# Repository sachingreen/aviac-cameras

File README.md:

# Aviac cameras

One repository for Aviac Technologies' drone camera payloads. Each camera has its own folder under `cameras/`.
The scripts that generate the schematic, board, 3D model, renders and teardown page are written to be reused:
a new camera starts from an existing folder and changes the parts list, layout and dimensions.

| Camera | Folder | State |
| --- | --- | --- |
| 6-band crop-mapping camera (IMX565 + 3 x Mira220, Jetson Orin Nano) | `cameras/6band/` | Concept model, schematic passes ERC, board is a first routing pass. Not ready for manufacture. |
| Duo: compact stereo box for spray drones (2 x Mira220, Jetson Orin Nano, no fan) | `cameras/duo/` | Concept model, cooling and stereo calculations, spray-check method. Uses the shared carrier with two camera ports fitted. |

Shared between cameras:

| Path | What it is |
| --- | --- |
| `boards/orin-carrier/` | Jetson Orin Nano carrier: netlist (`design.py`), placement, routing, KiCad project, BOM per camera (`variants.py`) |
| `boards/mira220-module/` | Mira220 camera module extracted from the SincereFirst schematic, with the hardware trigger added |
| `toolkit/kicad/` | Schematic generator and KiCad library helpers used by every board |
| `toolkit/render/` | Blender studio renderer and denoiser used by every camera |

## What each camera folder holds

| Path | What it is |
| --- | --- |
| `docs/` | Interface findings and design notes |
| `refs/` | Supplied schematics, datasheets |
| `mechanical/` | `build_model.py` (CadQuery), outputs in `out/` |
| `renders/` | Finished studio renders |
| `teardown/` | Interactive teardown page: `src/`, `build.mjs`, built page in `dist/` |

## Rebuilding

Tools: KiCad 8, Python 3 with CadQuery, Blender 4, Node 20, Java (for the Freerouting autorouter), Intel Open Image Denoise.

```bash
python3 toolkit/kicad/gen_sch.py boards/orin-carrier
```

```bash
cd boards/orin-carrier && /usr/bin/python3 gen_pcb.py && /usr/bin/python3 route.py --export
```

```bash
python3 toolkit/kicad/gen_sch.py boards/mira220-module
```

Each camera's README has its model, render and page steps. The 3D board file (`*.glb`) is not stored; export it with `kicad-cli pcb export glb --subst-models --include-tracks`.

## Credits

- Teardown page structure and `teardown/kit/` files: [elvarofficial/teardown](https://github.com/elvarofficial/teardown), MIT.
- Jetson socket and M.2 footprints, module pin names: [antmicro/jetson-orin-baseboard](https://github.com/antmicro/jetson-orin-baseboard), Apache-2.0.

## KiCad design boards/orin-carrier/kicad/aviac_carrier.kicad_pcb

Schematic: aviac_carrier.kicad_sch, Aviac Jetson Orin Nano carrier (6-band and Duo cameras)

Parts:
C1, C2, C5, C7, C10, C15, C16, C19, C29, C61: 100n; C_0603_1608Metric; MPN CAP 100n 50V X7R 0603
C3, C4: 22u; C_1210_3225Metric; MPN CAP 22u 50V X7R 1210
C6, C23, C31, C33, C35, C37, C38, C39, C40, C41, C43, C46, C47, C48, C51, C52, C54, C60, C62: 100n; C_0402_1005Metric; MPN CAP 100n 16V X7R 0402
C8, C17: 1u; C_0603_1608Metric; MPN CAP 1u 16V X7R 0603
C9, C18: 10u; C_1210_3225Metric; MPN CAP 10u 50V X7R 1210
C11, C20: 22p; C_0402_1005Metric; MPN CAP 22p 50V C0G 0402
C12, C13, C14, C27, C28: 22u; C_1210_3225Metric; MPN CAP 22u 25V X7R 1210
C21, C22, C58, C59: 22u; C_0805_2012Metric; MPN CAP 22u 10V X5R 0805
C24: 1u; C_0603_1608Metric; MPN CAP 1u 25V X7R 0603
C25, C53: 10n; C_0402_1005Metric; MPN CAP 10n 16V X7R 0402
C26, C55: 2u2; C_0603_1608Metric; MPN CAP 2u2 10V X7R 0603
C30, C32, C34, C36, C50: 10u; C_0603_1608Metric; MPN CAP 10u 10V X5R 0603
C42: 4u7; C_0603_1608Metric; MPN CAP 4u7 10V X5R 0603
C44, C45: 12p; C_0402_1005Metric; MPN CAP 12p 50V C0G 0402
C49: 100p; C_0402_1005Metric; MPN CAP 100p 50V C0G 0402
C56, C57: 220n; C_0402_1005Metric; MPN CAP 220n 10V X5R 0402
D1: SMBJ26CA; D_SMB; MPN SMBJ26CA
D2: green; LED_0402_1005Metric; MPN LTST-C281KGKT
D3: amber; LED_0402_1005Metric; MPN LTST-C281KFKT
D4: PESD3V3L4UG; SOT-353_SC-70-5; MPN PESD3V3L4UG,115
FB1, FB2, FB3, FB4, FB5: 600R 1A; L_0603_1608Metric; MPN BLM18KG601SN1D
H1, H2: M2.5 standoff 6.5 mm; MountingHole_2.7mm_M2.5_Pad; MPN 9774065151R
H3: M2 SSD standoff 2230; MountingHole_2.2mm_M2_DIN965_Pad; MPN 9774025243R
H4, H5, H6, H7: M2.5 board mount; MountingHole_2.7mm_M2.5_Pad
J1: XT30PW-M; AMASS_XT30PW-M_1x02_P2.50mm_Horizontal; MPN XT30PW-M
J2: Jetson Orin Nano 8GB; TE_2309413; MPN 2309413-1
J3: CAM0: RGB, IMX565 (via adapter) (mirrored); Hirose_FH12-22S-0.5SH_1x22-1MP_P0.50mm_Horizontal; MPN FH12-22S-0.5SH(55)
J4: CAM1: red edge, Mira220; Hirose_FH12-22S-0.5SH_1x22-1MP_P0.50mm_Horizontal; MPN FH12-22S-0.5SH(55)
J5: CAM2: NIR, Mira220 (mirrored); Hirose_FH12-22S-0.5SH_1x22-1MP_P0.50mm_Horizontal; MPN FH12-22S-0.5SH(55)
J6: CAM3: extended NIR, Mira220; Hirose_FH12-22S-0.5SH_1x22-1MP_P0.50mm_Horizontal; MPN FH12-22S-0.5SH(55)
J7: SWD (Tag-Connect); Tag-Connect_TC2030-IDC-NL_2x03_P1.27mm_Vertical; MPN (no part: PCB pads for TC2030-IDC-NL ca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
J8: TELEM (MAVLink); JST_GH_SM06B-GHS-TB_1x06-1MP_P1.25mm_Horizontal; MPN SM06B-GHS-TB
J9: CAM TRIGGER; JST_GH_SM04B-GHS-TB_1x04-1MP_P1.25mm_Horizontal; MPN SM04B-GHS-TB
J10: GNSS ANT; U.FL_Hirose_U.FL-R-SMT-1_Vertical; MPN U.FL-R-SMT-1(10)
J11: M.2 Key M; Bus_M.2_Socket_Key_M_TE_1-2199230-6; MPN 1-2199230-6
J12: USB-C; USB_C_Receptacle_GCT_USB4105-xx-A_16P_TopMnt_Horizontal; MPN USB4105-GF-A
J13: DLS; JST_GH_SM05B-GHS-TB_1x05-1MP_P1.25mm_Horizontal; MPN SM05B-GHS-TB
J14: DEBUG UART 1V8 DNP; PinHeader_1x03_P1.27mm_Vertical; MPN (not fitted); not fitted
L1: 6u8 8A; L_Bourns_SRP6060FA; MPN SRP6060FA-6R8M
L2: 6u8 3.9A; L_Coilcraft_XAL4030-XXX; MPN XAL4030-682ME
L3: 27n; L_0402_1005Metric; MPN LQG15HS27NJ02D
Q1: BSC028N06LS3; TDSON-8-1; MPN BSC028N06LS3GATMA1
Q2: 2N7002; SOT-23; MPN 2N7002NXAKR
R1, R3, R5, R7, R8, R10, R12, R14, R16, R18, R22, R26, R30, R42, R44, R51, R55: 100k; R_0402_1005Metric; MPN RES 100k 1% 0402
R2: 6k8; R_0402_1005Metric; MPN RES 6k8 1% 0402
R4: 16k2; R_0402_1005Metric; MPN RES 16k2 1% 0402
R6: 15k4; R_0402_1005Metric; MPN RES 15k4 1% 0402
R9: 43k2; R_0402_1005Metric; MPN RES 43k2 1% 0402
R11, R17, R34, R40, R45: 10k; R_0402_1005Metric; MPN RES 10k 1% 0402
R13, R37, R38, R39, R41: 1k; R_0402_1005Metric; MPN RES 1k 1% 0402
R15, R47, R48: 47k; R_0402_1005Metric; MPN RES 47k 1% 0402
R19, R20, R23, R24, R27, R28, R31, R32, R53, R54: 2k2; R_0402_1005Metric; MPN RES 2k2 1% 0402
R21, R25, R29, R33: 33R; R_0402_1005Metric; MPN RES 33R 1% 0402
R35, R36: 2k2 DNP; R_0402_1005Metric; MPN RES 2k2 1% 0402; not fitted
R43: 100R; R_0402_1005Metric; MPN RES 100R 1% 0402
R46: 10R; R_0402_1005Metric; MPN RES 10R 1% 0402
R49, R50: 5k1; R_0402_1005Metric; MPN RES 5k1 1% 0402
R52: 56k; R_0402_1005Metric; MPN RES 56k 1% 0402
SW1: RECOVERY; SW_SPST_B3U-1000P-B; MPN B3U-1000P-B
SW2: RESET; SW_SPST_B3U-1000P-B; MPN B3U-1000P-B
TP1: VSYS; TestPoint_Pad_D1.0mm
TP2: 3V3; TestPoint_Pad_D1.0mm
TP3: 1V8; TestPoint_Pad_D1.0mm
TP4: GND; TestPoint_Pad_D1.0mm
U1: LM74700-Q1; SOT-23-6; MPN LM74700QDBVRQ1
U2: LMR33640ADDA; Texas_HSOP-8-1EP_3.9x4.9mm_P1.27mm_ThermalVias; MPN LMR33640ADDAR
U3: LMR33630ADDA; Texas_HSOP-8-1EP_3.9x4.9mm_P1.27mm_ThermalVias; MPN LMR33630ADDAR
U4: LP2985-18; SOT-23-5; MPN LP2985-18DBVR
U5: TCA9548A; TSSOP-24_4.4x7.8mm_P0.65mm; MPN TCA9548APWR
U6: STM32G0B1CBT6; LQFP-48_7x7mm_P0.5mm; MPN STM32G0B1CBT6
U7: TXS0102; VSSOP-8_2.3x2mm_P0.5mm; MPN TXS0102DCUR
U8: 74LVC2G17; SOT-363_SC-70-6; MPN SN74LVC2G17DCKR
U9: MAX-M10S; ublox_MAX; MPN MAX-M10S-00B
U10: ICM-42688-P; LGA-14_3x2.5mm_P0.5mm_LayoutBorder3x4y; MPN ICM-42688-P
U11: USBLC6-2SC6; SOT-23-6; MPN USBLC6-2SC6
U12: M24C02-F; SOIC-8_3.9x4.9mm_P1.27mm; MPN M24C02-FMN6TP
Y1: 8MHz; Crystal_SMD_3225-4Pin_3.2x2.5mm; MPN ABM8-8.000MHZ-10-D1G-T

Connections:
+1V8: C26.1, C38.1, C39.1, C40.1, C41.1, C42.1, C46.1, C48.1, C52.1, C54.1, C55.1, C62.1, J7.1, J13.1, R16.1, R19.1, R20.1, R23.1, R24.1, R27.1, R28.1, R31.1, R32.1, R34.1, R35.1, R36.1, R40.1, R53.1, R54.1, R55.1, TP3.1, U4.5 (VOUT), U5.24 (VCC), U6.4 (VBAT), U6.5 (VREF+), U6.6 (VDD), U7.3 (VCCA), U8.5 (VCC), U9.6 (V_BCKP), U9.7 (VCC_IO), U10.5 (VDDIO), U10.8 (VDD), U12.1 (E0), U12.2 (E1), U12.3 (E2), U12.8 (VCC)
+3V3: C20.1, C21.1, C22.1, C23.1, C47.1, C58.1, C59.1, C60.1, D2.2 (A), FB1.1, FB2.1, FB3.1, FB4.1, FB5.1, J11.2 (3.3V), J11.4 (3.3V), J11.12 (3.3V), J11.14 (3.3V), J11.16 (3.3V), J11.18 (3.3V), J11.70 (3.3V), J11.72 (3.3V), J11.74 (3.3V), L2.2, R8.1, R39.1, R45.1, R47.1, R48.1, TP2.1, U7.7 (VCCB)
CAM0_3V3: C30.1, C31.1, FB1.2, J3.1
CAM0_CLK_N: J2.10 (CSI0_CLK_N), J3.15
CAM0_CLK_P: J2.12 (CSI0_CLK_P), J3.14
CAM0_D0_N: J2.4 (CSI0_D0_N), J3.21
CAM0_D0_P: J2.6 (CSI0_D0_P), J3.20
CAM0_D1_N: J2.16 (CSI0_D1_N), J3.18
CAM0_D1_P: J2.18 (CSI0_D1_P), J3.17
CAM0_EN: J2.114 (CAM0_PWDN), J3.6, R18.1
CAM0_SCL: J3.3, R19.2, U5.5 (SC0)
CAM0_SDA: J3.2, R20.2, U5.4 (SD0)
CAM0_TRIG: J3.5, R21.2
CAM1_3V3: C32.1, C33.1, FB2.2, J4.22
CAM1_CLK_N: J2.9 (CSI1_CLK_N), J4.8
CAM1_CLK_P: J2.11 (CSI1_CLK_P), J4.9
CAM1_D0_N: J2.3 (CSI1_D0_N), J4.2
CAM1_D0_P: J2.5 (CSI1_D0_P), J4.3
CAM1_D1_N: J2.15 (CSI1_D1_N), J4.5
CAM1_D1_P: J2.17 (CSI1_D1_P), J4.6
CAM1_EN: J2.120 (CAM1_PWDN), J4.17, R22.1
CAM1_SCL: J4.20, R23.2, U5.7 (SC1)
CAM1_SDA: J4.21, R24.2, U5.6 (SD1)
CAM1_TRIG: J4.18, R25.2
CAM2_3V3: C34.1, C35.1, FB3.2, J5.1
CAM2_CLK_N: J2.28 (CSI2_CLK_N), J5.15
CAM2_CLK_P: J2.30 (CSI2_CLK_P), J5.14
CAM2_D0_N: J2.22 (CSI2_D0_N), J5.21
CAM2_D0_P: J2.24 (CSI2_D0_P), J5.20
CAM2_D1_N: J2.34 (CSI2_D1_N), J5.18
CAM2_D1_P: J2.36 (CSI2_D1_P), J5.17
CAM2_EN: J2.124 (GPIO02), J5.6, R26.1
CAM2_SCL: J5.3, R27.2, U5.9 (SC2)
CAM2_SDA: J5.2, R28.2, U5.8 (SD2)
CAM2_TRIG: J5.5, R29.2
CAM3_3V3: C36.1, C37.1, FB4.2, J6.22
CAM3_CLK_N: J2.27 (CSI3_CLK_N), J6.8
CAM3_CLK_P: J2.29 (CSI3_CLK_P), J6.9
CAM3_D0_N: J2.21 (CSI3_D0_N), J6.2
CAM3_D0_P: J2.23 (CSI3_D0_P), J6.3
CAM3_D1_N: J2.33 (CSI3_D1_N), J6.5
CAM3_D1_P: J2.35 (CSI3_D1_P), J6.6
CAM3_EN: J2.126 (GPIO03), J6.17, R30.1
CAM3_SCL: J6.20, R31.2, U5.11 (SC3)
CAM3_SDA: J6.21, R32.2, U5.10 (SD3)
CAM3_TRIG: J6.18, R33.2
DBG_RX: J2.238 (UART2_RXD), J14.2
DBG_TX: J2.236 (UART2_TXD), J14.1
DLS_INT: J13.4, R55.2, U6.21 (PB2)
DLS_SCL: J13.2, R53.2, U6.47 (PB8)
DLS_SDA: J13.3, R54.2, U6.48 (PB9)
FC_FB_GATE: Q2.1 (G), R44.1, U6.20 (PB1)
FC_FB_OUT: D4.5 (K4), J9.2, Q2.3 (D), R45.2
FC_TRIG_1V8: U6.12 (PA1), U8.6
FC_TRIG_IN: D4.4 (K3), J9.1, R41.1
FC_TRIG_IN_F: C49.1, R41.2, R42.1, U8.1
FORCE_RECOVERY_N: J2.214 (FORCE_RECOVERY*), SW1.1
FRAME_SYNC: J2.216 (GPIO11/CLK), U6.44 (PB5)
GND: C2.2, C3.2, C4.2, C5.2, C6.2, C8.2, C9.2, C10.2, C12.2, C13.2, C14.2, C15.2, C17.2, C18.2, C19.2, C21.2, C22.2, C23.2, C24.2, C25.2, C26.2, C27.2, C28.2, C29.2, C30.2, C31.2, C32.2, C33.2, C34.2, C35.2, C36.2, C37.2, C38.2, C39.2, C40.2, C41.2, C42.2, C43.2, C44.2, C45.2, C46.2, C47.2, C48.2, C49.2, C50.2, C51.2, C52.2, C53.2, C54.2, C55.2, C58.2, C59.2, C60.2, C61.2, C62.2, D1.2 (A2), D4.2 (A), H1.1, H2.1, H3.1, H4.1, H5.1, H6.1, H7.1, J1.2, J2.1 (GND), J2.2 (GND), J2.7 (GND), J2.8 (GND), J2.13 (GND), J2.14 (GND), J2.19 (GND), J2.20 (GND), J2.25 (GND), J2.26 (GND), J2.31 (GND), J2.32 (GND), J2.37 (GND), J2.38 (GND), J2.43 (GND), J2.44 (GND), J2.49 (GND), J2.50 (GND), J2.55 (GND), J2.56 (GND), J2.61 (GND), J2.62 (GND), J2.67 (GND), J2.68 (GND), J2.73 (GND), J2.74 (GND), J2.79 (GND), J2.80 (GND), J2.85 (GND), J2.86 (GND), J2.102 (GND), J2.107 (GND), J2.113 (GND), J2.119 (GND), J2.125 (GND), J2.129 (GND), J2.132 (GND), J2.135 (GND), J2.138 (GND), J2.141 (GND), J2.144 (GND), J2.146 (GND), J2.147 (GND), J2.152 (GND), J2.153 (GND), J2.158 (GND), J2.159 (GND), J2.164 (GND), J2.165 (GND), J2.170 (GND), J2.171 (GND), J2.176 (GND), J2.177 (GND), J2.200 (GND), J2.201 (GND), J2.231 (GND), J2.241 (GND), J2.242 (GND), J2.243 (GND), J2.244 (GND), J2.245 (GND), J2.246 (GND), J2.247 (GND), J2.248 (GND), J2.249 (GND), J2.250 (GND), J3.4, J3.7, J3.10, J3.13, J3.16, J3.19, J3.22, J3.MP (MountPin), J4.1, J4.4, J4.7, J4.10, J4.13, J4.16, J4.19, J4.MP (MountPin), J5.4, J5.7, J5.10, J5.13, J5.16, J5.19, J5.22, J5.MP (MountPin), J6.1, J6.4, J6.7, J6.10, J6.13, J6.16, J6.19, J6.MP (MountPin), J7.5, J8.6, J8.MP (MountPin), J9.4, J9.MP (MountPin), J10.2 (Ext), J11.1 (GND), J11.3 (GND), J11.9 (GND), J11.15 (GND), J11.21 (GND), J11.27 (GND), J11.33 (GND), J11.39 (GND), J11.45 (GND), J11.51 (GND), J11.57 (GND), J11.71 (GND), J11.73 (GND), J11.75 (GND), J11.MP1, J11.MP2, J12.A1 (GND), J12.A12 (GND), J12.B1 (GND), J12.B12 (GND), J12.S1 (SHIELD), J13.5, J13.MP (MountPin), J14.3, Q2.2 (S), R2.2, R4.2, R6.2, R9.2, R12.2, R13.2, R15.2, R18.2, R22.2, R26.2, R30.2, R42.2, R44.2, R49.2, R50.2, R52.2, SW1.2, SW2.2, TP4.1, U1.2 (GND), U2.1 (GND), U2.9 (GND), U3.1 (GND), U3.9 (GND), U4.2 (GND), U5.1 (A0), U5.2 (A1), U5.12 (GND), U5.21 (A2), U6.7 (VSS), U7.2 (GND), U8.2 (GND), U9.1 (GND), U9.10 (GND), U9.12 (GND), U9.15 (VIO_SEL), U10.6 (GND), U11.2 (GND), U12.4 (VSS), U12.7 (~WC), Y1.2, Y1.4
GNSS_BIAS: C53.1, L3.1, R46.2
GNSS_RF: J10.1 (In), L3.2, U9.11 (RF_IN)
GNSS_RXD: U6.22 (PB10), U9.3 (RXD)
GNSS_TXD: U6.23 (PB11), U9.2 (TXD)
GNSS_VCC: C50.1, C51.1, FB5.2, U9.8 (VCC)
GNSS_VCC_RF: R46.1, U9.14 (VCC_RF)
I2C_CAM_SCL: J2.213 (CAM_I2C_SCL), R35.2, U5.22 (SCL)
I2C_CAM_SDA: J2.215 (CAM_I2C_SDA), R36.2, U5.23 (SDA)
I2C_ID_SCL: J2.232 (I2C2_SCL), U12.6 (SCL)
I2C_ID_SDA: J2.234 (I2C2_SDA), U12.5 (SDA)
I2C_MUX_RST_N: R34.2, U5.3 (~RESET)
IMU_CS_N: U6.15 (PA4), U10.12 (AP_CS)
IMU_INT1: U6.19 (PB0), U10.4 (INT1)
IMU_MISO: U6.17 (PA6), U10.1 (AP_SDO)
IMU_MOSI: U6.18 (PA7), U10.14 (AP_SDI)
IMU_SCK: U6.16 (PA5), U10.13 (AP_SCLK)
LDO_BP: C25.1, U4.4 (BP)
LED_PWR_K: D2.1 (K), R13.1
LED_STAT_A: D3.2 (A), R39.2
LED_STAT_K: D3.1 (K), U6.24 (PB12)
MCU_BOOT_REQ: J2.228 (GPIO13/PWM), R38.1
MCU_NRST: C43.1, J7.3, R37.2, U6.10 (PF2)
MCU_NRST_REQ: J2.218 (GPIO12/PWM), R37.1
MCU_OSC_IN: C44.1, U6.8 (PF0), Y1.1
MCU_OSC_OUT: C45.1, U6.9 (PF1), Y1.3
MCU_UART_RX: J2.99 (UART0_TXD), U6.14 (PA3)
MCU_UART_TX: J2.101 (UART0_RXD), U6.13 (PA2)
P3V3_BOOT: C16.1, U3.7 (BOOT)
P3V3_EN: R11.2, R12.1, U3.3 (EN)
P3V3_FB: C20.2, R8.2, R9.1, U3.5 (FB)
P3V3_PG: R10.2, U3.4 (PG)
P3V3_SW: C16.2, L2.1, U3.8 (SW)
P3V3_VCC: C17.1, R10.1, U3.6 (VCC)
PCIE_CLKREQ_N: J2.180 (PCIE0_CLKREQ*), J11.52 (~CLKREQ), R47.2
PCIE_CLK_N: J2.160 (PCIE0_CLK_N), J11.53 (REFCLKn)
PCIE_CLK_P: J2.162 (PCIE0_CLK_P), J11.55 (REFCLKp)
PCIE_RST_N: J2.181 (PCIE0_RST*), J11.50 (~PERST)
PCIE_RX_N: J2.131 (PCIE0_RX0_N), J11.41 (PERn0/SATA-B+)
PCIE_RX_P: J2.133 (PCIE0_RX0_P), J11.43 (PERp0/SATA-B-)
PCIE_TX_C_N: C56.1, J2.134 (PCIE0_TX0_N)
PCIE_TX_C_P: C57.1, J2.136 (PCIE0_TX0_P)
PCIE_TX_N: C56.2, J11.47 (PETn0/SATA-A-)
PCIE_TX_P: C57.2, J11.49 (PETp0/SATA-A+)
PCIE_WAKE_N: J2.179 (PCIE_WAKE*), J11.54 (~PEWAKE), R48.2
POWER_EN: J2.237 (POWER_EN), R14.2, R15.1, U6.25 (PB13)
PPS_1V8: J2.211 (GPIO09/AUD_MCLK), U6.37 (PA15), U8.3, U9.4 (TIMEPULSE)
PPS_BUF: R43.1, U8.4
PPS_OUT: J9.3, R43.2
RP_GATE: Q1.4 (G), U1.5 (GATE)
RP_VCAP: C1.1, U1.1 (VCAP)
SHUTDOWN_REQ_N: J2.233 (SHUTDOWN_REQ*), R16.2, U6.26 (PB14)
SWCLK_BOOT0: J7.4, R38.2, U6.36 (PA14)
SWDIO: J7.2, U6.35 (PA13)
SYS_RESET_N: J2.239 (SYS_RESET*), R11.1, R17.1, SW2.1
SYS_RESET_SENSE: R17.2, U6.27 (PB15)
TELEM_OE: R40.2, U7.6 (OE)
TELEM_RX_1V8: J2.205 (UART1_RXD), U7.4 (A2)
TELEM_RX_3V3: D4.1 (K1), J8.2, U7.1 (B2)
TELEM_TX_1V8: J2.203 (UART1_TXD), U7.5 (A1)
TELEM_TX_3V3: D4.3 (K2), J8.3, U7.8 (B1)
TRIG0: R21.1, U6.28 (PA8)
TRIG1: R25.1, U6.29 (PA9/UCPD1_DBCC1)
TRIG2: R29.1, U6.32 (PA10/UCPD1_DBCC2)
TRIG3: R33.1, U6.33 (PA9/PA11)
USB_CC1: J12.A5 (CC1), R49.1
USB_CC2: J12.B5 (CC2), R50.1
USB_CON_D_N: J12.A7 (D-), J12.B7 (D-), U11.1 (I/O1)
USB_CON_D_P: J12.A6 (D+), J12.B6 (D+), U11.3 (I/O2)
USB_D_N: J2.109 (USB0_D_N), U11.6 (I/O1)
USB_D_P: J2.111 (USB0_D_P), U11.4 (I/O2)
USB_VBUS: C61.1, J12.A4 (VBUS), J12.A9 (VBUS), J12.B4 (VBUS), J12.B9 (VBUS), R51.1, U11.5 (VBUS)
USB_VBUS_DET: J2.118 (GPIO01/CLK), R51.2, R52.1
VBAT: C3.1, C4.1, C5.1, C9.1, C10.1, C18.1, C19.1, Q1.5 (D), R1.1, R3.1, U1.4 (CATHODE), U2.2 (VIN), U3.2 (VIN)
VBAT_IN: C1.2, C2.1, D1.1 (A1), J1.1, Q1.1 (S), Q1.2 (S), Q1.3 (S), U1.3 (EN), U1.6 (ANODE)
VBAT_SENSE: C6.1, R1.2, R2.1, U6.11 (PA0)
VSYS: C11.1, C12.1, C13.1, C14.1, C15.1, C24.1, C27.1, C28.1, C29.1, J2.251 (VDD_IN), J2.252 (VDD_IN), J2.253 (VDD_IN), J2.254 (VDD_IN), J2.255 (VDD_IN), J2.256 (VDD_IN), J2.257 (VDD_IN), J2.258 (VDD_IN), J2.259 (VDD_IN), J2.260 (VDD_IN), L1.2, R5.1, R14.1, TP1.1, U4.1 (VIN), U4.3 (ON/~OFF)
VSYS_BOOT: C7.1, U2.7 (BOOT)
VSYS_EN: R3.2, R4.1, U2.3 (EN)
VSYS_FB: C11.2, R5.2, R6.1, U2.5 (FB)
VSYS_PG: R7.2, U2.4 (PG)
VSYS_SW: C7.2, L1.1, U2.8 (SW)
VSYS_VCC: C8.1, R7.1, U2.6 (VCC)

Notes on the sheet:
POWER INPUT 3S-6S: REVERSE-POLARITY AND SURGE PROTECTION
7.5 V 4 A MODULE SUPPLY (VSYS)
3.3 V 3 A PERIPHERAL SUPPLY AND 1.8 V ALWAYS-ON
JETSON ORIN NANO MODULE
MODULE POWER SEQUENCING, RESET AND RECOVERY
CAMERA PORTS: 4 x 2-LANE MIPI CSI-2, 22-PIN FPC
CAMERA I2C SWITCH
SYNC MICROCONTROLLER
TRIGGER FAN-OUT AND AUTOPILOT INTERFACE
GNSS RECEIVER WITH PPS
INERTIAL SENSOR
M.2 2230 NVME STORAGE
USB-C: FLASHING AND DATA
DLS PORT, DEBUG, ID EEPROM, MECHANICAL

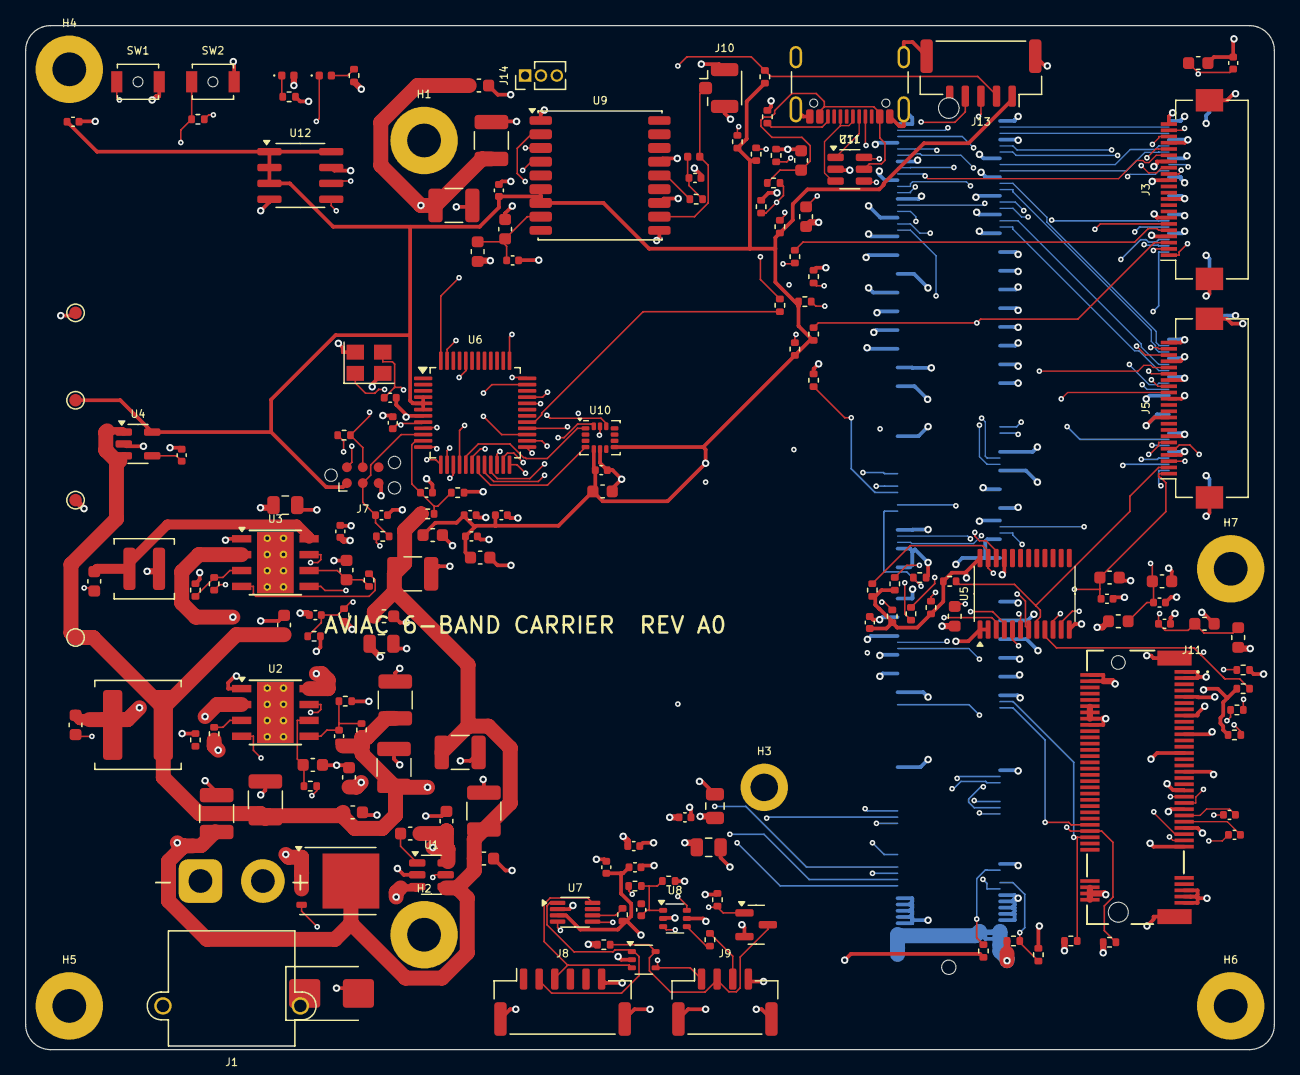
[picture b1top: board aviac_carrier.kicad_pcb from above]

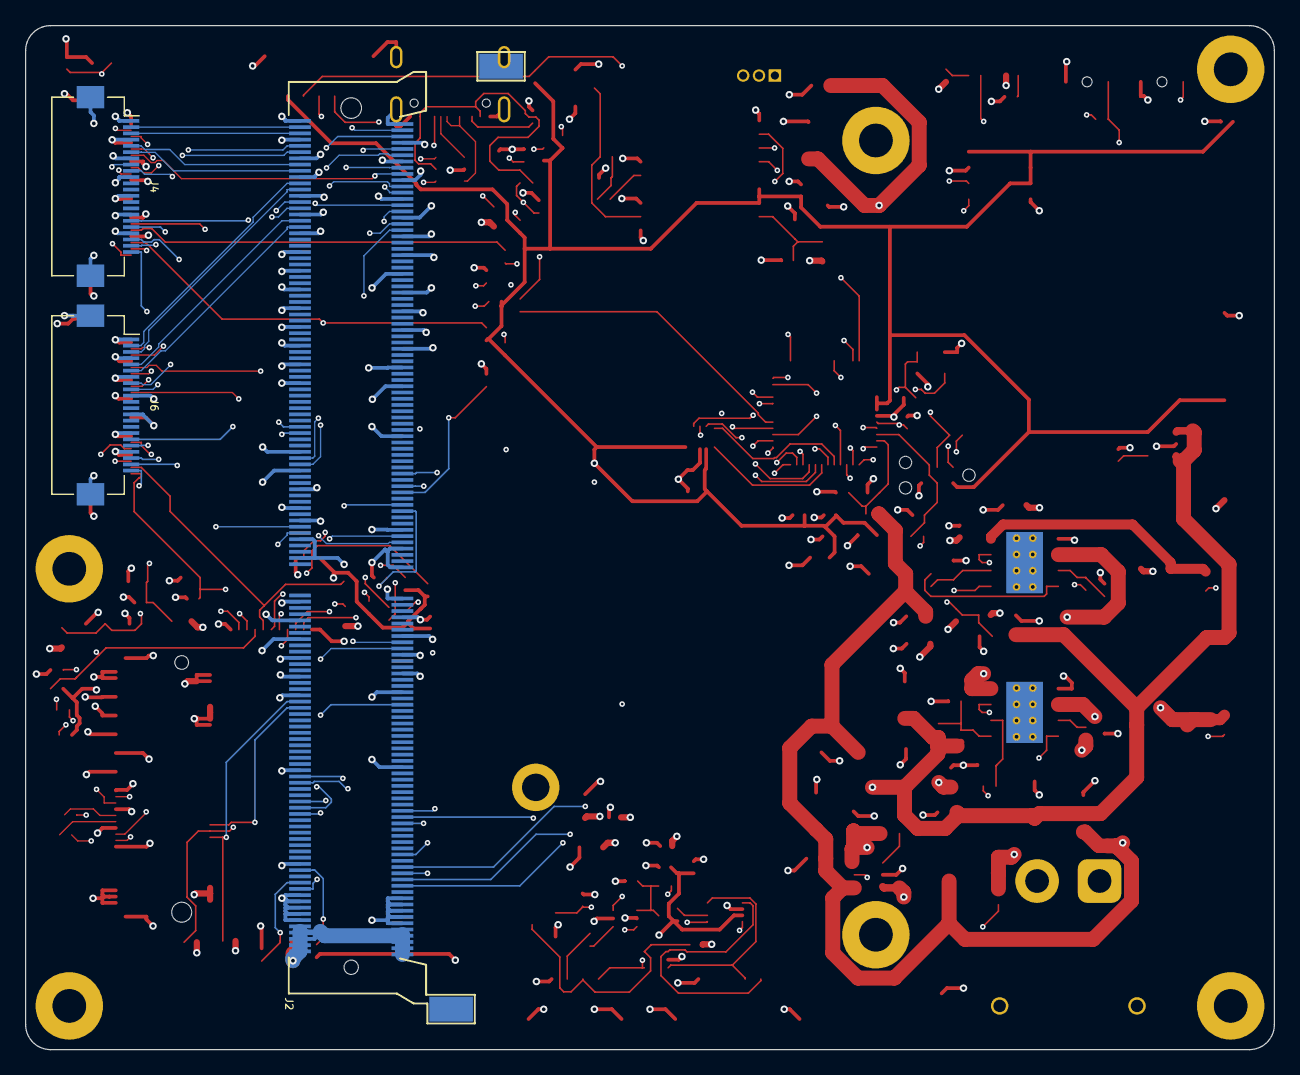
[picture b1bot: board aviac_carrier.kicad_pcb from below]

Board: 6 copper layers, 100.0 x 82.0 mm, 171 parts (3 on the bottom side), 141 nets.

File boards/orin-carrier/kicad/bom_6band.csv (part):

References,Qty,Value,Manufacturer part,Manufacturer,Description,Footprint
C1 C2 C5 C7 C10 C15 C16 C19 C29 C61,10,100n,CAP 100n 50V X7R 0603,generic (Murata GRM / Samsung CL),Capacitor 100n 50V X7R 0603,C_0603_1608Metric
C3 C4,2,22u,CAP 22u 50V X7R 1210,generic (Murata GRM / Samsung CL),Capacitor 22u 50V X7R 1210,C_1210_3225Metric
C6 C23 C31 C33 C35 C37 C38 C39 C40 C41 C43 C46 C47 C48 C51 C52 C54 C60 C62,19,100n,CAP 100n 16V X7R 0402,generic (Murata GRM / Samsung CL),Capacitor 100n 16V X7R 0402,C_0402_1005Metric
C8 C17,2,1u,CAP 1u 16V X7R 0603,generic (Murata GRM / Samsung CL),Capacitor 1u 16V X7R 0603,C_0603_1608Metric
C9 C18,2,10u,CAP 10u 50V X7R 1210,generic (Murata GRM / Samsung CL),Capacitor 10u 50V X7R 1210,C_1210_3225Metric
C11 C20,2,22p,CAP 22p 50V C0G 0402,generic (Murata GRM / Samsung CL),Capacitor 22p 50V C0G 0402,C_0402_1005Metric
C12 C13 C14 C27 C28,5,22u,CAP 22u 25V X7R 1210,generic (Murata GRM / Samsung CL),Capacitor 22u 25V X7R 1210,C_1210_3225Metric
C21 C22 C58 C59,4,22u,CAP 22u 10V X5R 0805,generic (Murata GRM / Samsung CL),Capacitor 22u 10V X5R 0805,C_0805_2012Metric
C24,1,1u,CAP 1u 25V X7R 0603,generic (Murata GRM / Samsung CL),Capacitor 1u 25V X7R 0603,C_0603_1608Metric
C25 C53,2,10n,CAP 10n 16V X7R 0402,generic (Murata GRM / Samsung CL),Capacitor 10n 16V X7R 0402,C_0402_1005Metric
C26 C55,2,2u2,CAP 2u2 10V X7R 0603,generic (Murata GRM / Samsung CL),Capacitor 2u2 10V X7R 0603,C_0603_1608Metric
C30 C32 C34 C36 C50,5,10u,CAP 10u 10V X5R 0603,generic (Murata GRM / Samsung CL),Capacitor 10u 10V X5R 0603,C_0603_1608Metric
C42,1,4u7,CAP 4u7 10V X5R 0603,generic (Murata GRM / Samsung CL),Capacitor 4u7 10V X5R 0603,C_0603_1608Metric
C44 C45,2,12p,CAP 12p 50V C0G 0402,generic (Murata GRM / Samsung CL),Capacitor 12p 50V C0G 0402,C_0402_1005Metric
C49,1,100p,CAP 100p 50V C0G 0402,generic (Murata GRM / Samsung CL),Capacitor 100p 50V C0G 0402,C_0402_1005Metric
C56 C57,2,220n,CAP 220n 10V X5R 0402,generic (Murata GRM / Samsung CL),Capacitor 220n 10V X5R 0402,C_0402_1005Metric
D1,1,SMBJ26CA,SMBJ26CA,Littelfuse,"TVS 26 V stand-off, bidirectional, 600 W",D_SMB
D2,1,green,LTST-C281KGKT,Lite-On,"LED green 0402, peripherals powered",LED_0402_1005Metric
D3,1,amber,LTST-C281KFKT,Lite-On,"LED amber 0402, sync status",LED_0402_1005Metric
D4,1,PESD3V3L4UG,"PESD3V3L4UG,115",Nexperia,4-line ESD protection for the autopilot connectors,SOT-353_SC-70-5
FB1 FB2 FB3 FB4 FB5,5,600R 1A,BLM18KG601SN1D,Murata,"Ferrite bead 600 ohm at 100 MHz, 1.3 A, 0603",L_0603_1608Metric
J1,1,XT30PW-M,XT30PW-M,AMASS,"Battery input 3S-6S (9-25.2 V), 15 A connector",AMASS_XT30PW-M_1x02_P2.50mm_Horizontal
J2,1,Jetson Orin Nano 8GB,2309413-1,TE Connectivity,"260-pin SO-DIMM socket, 9.2 mm, for Jetson Orin Nano module",TE_2309413
J3,1,"CAM0: RGB, IMX565 (via adapter) (mirrored)",FH12-22S-0.5SH(55),Hirose,"FPC connector 22-pin 0.5 mm, bottom contact",Hirose_FH12-22S-0.5SH_1x22-1MP_P0.50mm_Horizontal
J4,1,"CAM1: red edge, Mira220",FH12-22S-0.5SH(55),Hirose,"FPC connector 22-pin 0.5 mm, bottom contact",Hirose_FH12-22S-0.5SH_1x22-1MP_P0.50mm_Horizontal
J5,1,"CAM2: NIR, Mira220 (mirrored)",FH12-22S-0.5SH(55),Hirose,"FPC connector 22-pin 0.5 mm, bottom contact",Hirose_FH12-22S-0.5SH_1x22-1MP_P0.50mm_Horizontal
J6,1,"CAM3: extended NIR, Mira220",FH12-22S-0.5SH(55),Hirose,"FPC connector 22-pin 0.5 mm, bottom contact",Hirose_FH12-22S-0.5SH_1x22-1MP_P0.50mm_Horizontal
J8,1,TELEM (MAVLink),SM06B-GHS-TB,JST,"Autopilot TELEM port, Pixhawk pinout (pin 1 = 5 V not used)",JST_GH_SM06B-GHS-TB_1x06-1MP_P1.25mm_Horizontal
J9,1,CAM TRIGGER,SM04B-GHS-TB,JST,"Camera trigger in, exposure feedback out, PPS out",JST_GH_SM04B-GHS-TB_1x04-1MP_P1.25mm_Horizontal
J10,1,GNSS ANT,U.FL-R-SMT-1(10),Hirose,"U.FL antenna connector, active antenna on the top unit",U.FL_Hirose_U.FL-R-SMT-1_Vertical
J11,1,M.2 Key M,1-2199230-6,TE Connectivity,"M.2 Key-M socket, PCIe x1 (lane 0) to NVMe 2230",Bus_M.2_Socket_Key_M_TE_1-2199230-6
J12,1,USB-C,USB4105-GF-A,GCT,"USB-C receptacle, USB 2.0, device mode for flashing and data",USB_C_Receptacle_GCT_USB4105-xx-A_16P_TopMnt_Horizontal
J13,1,DLS,SM05B-GHS-TB,JST,"Downwelling light sensor port (I2C at 1.8 V, read by the sync MCU)",JST_GH_SM05B-GHS-TB_1x05-1MP_P1.25mm_Horizontal
L1,1,6u8 8A,SRP6060FA-6R8M,Bourns,"Power inductor 6.8 uH, Isat 8 A, 6.6 x 6.4 x 5.8 mm",L_Bourns_SRP6060FA
L2,1,6u8 3.9A,XAL4030-682ME,Coilcraft,"Power inductor 6.8 uH, Isat 3.9 A, 4 x 4 x 3.1 mm",L_Coilcraft_XAL4030-XXX
L3,1,27n,LQG15HS27NJ02D,Murata,"RF inductor 27 nH, antenna bias feed",L_0402_1005Metric
Q1,1,BSC028N06LS3,BSC028N06LS3GATMA1,Infineon,"N-MOSFET 60 V 2.8 mOhm, ideal-diode pass element",TDSON-8-1
Q2,1,2N7002,2N7002NXAKR,Nexperia,"N-MOSFET, open-drain exposure feedback to autopilot",SOT-23
R1 R3 R5 R7 R8 R10 R12 R14 R16 R18 R22 R26 R30 R42 R44 R51 R55,17,100k,RES 100k 1% 0402,generic (Yageo RC / Vishay CRCW),Resistor 100k 1% 0402,R_0402_1005Metric
R2,1,6k8,RES 6k8 1% 0402,generic (Yageo RC / Vishay CRCW),Resistor 6k8 1% 0402,R_0402_1005Metric
R4,1,16k2,RES 16k2 1% 0402,generic (Yageo RC / Vishay CRCW),Resistor 16k2 1% 0402,R_0402_1005Metric
R6,1,15k4,RES 15k4 1% 0402,generic (Yageo RC / Vishay CRCW),Resistor 15k4 1% 0402,R_0402_1005Metric
R9,1,43k2,RES 43k2 1% 0402,generic (Yageo RC / Vishay CRCW),Resistor 43k2 1% 0402,R_0402_1005Metric
R11 R17 R34 R40 R45,5,10k,RES 10k 1% 0402,generic (Yageo RC / Vishay CRCW),Resistor 10k 1% 0402,R_0402_1005Metric
R13 R37 R38 R39 R41,5,1k,RES 1k 1% 0402,generic (Yageo RC / Vishay CRCW),Resistor 1k 1% 0402,R_0402_1005Metric
R15 R47 R48,3,47k,RES 47k 1% 0402,generic (Yageo RC / Vishay CRCW),Resistor 47k 1% 0402,R_0402_1005Metric
R19 R20 R23 R24 R27 R28 R31 R32 R53 R54,10,2k2,RES 2k2 1% 0402,generic (Yageo RC / Vishay CRCW),Resistor 2k2 1% 0402,R_0402_1005Metric
R21 R25 R29 R33,4,33R,RES 33R 1% 0402,generic (Yageo RC / Vishay CRCW),Resistor 33R 1% 0402,R_0402_1005Metric
R43,1,100R,RES 100R 1% 0402,generic (Yageo RC / Vishay CRCW),Resistor 100R 1% 0402,R_0402_1005Metric
R46,1,10R,RES 10R 1% 0402,generic (Yageo RC / Vishay CRCW),Resistor 10R 1% 0402,R_0402_1005Metric
R49 R50,2,5k1,RES 5k1 1% 0402,generic (Yageo RC / Vishay CRCW),Resistor 5k1 1% 0402,R_0402_1005Metric
R52,1,56k,RES 56k 1% 0402,generic (Yageo RC / Vishay CRCW),Resistor 56k 1% 0402,R_0402_1005Metric
SW1,1,RECOVERY,B3U-1000P-B,Omron,"Tactile switch, force-recovery (hold while powering on to flash)",SW_SPST_B3U-1000P-B
SW2,1,RESET,B3U-1000P-B,Omron,"Tactile switch, system reset",SW_SPST_B3U-1000P-B
U1,1,LM74700-Q1,LM74700QDBVRQ1,Texas Instruments,"Ideal-diode controller, reverse-polarity protection, 3.2-65 V",SOT-23-6
U2,1,LMR33640ADDA,LMR33640ADDAR,Texas Instruments,"Synchronous buck 3.8-36 V in, 4 A, 400 kHz",Texas_HSOP-8-1EP_3.9x4.9mm_P1.27mm_ThermalVias
U3,1,LMR33630ADDA,LMR33630ADDAR,Texas Instruments,"Synchronous buck 3.8-36 V in, 3 A, 400 kHz",Texas_HSOP-8-1EP_3.9x4.9mm_P1.27mm_ThermalVias
U4,1,LP2985-18,LP2985-18DBVR,Texas Instruments,"LDO 1.8 V 150 mA, 16 V in, always-on rail for the sync MCU",SOT-23-5
U5,1,TCA9548A,TCA9548APWR,Texas Instruments,"8-channel I2C switch (address 0x70), powered at 1.8 V so its pass gates translate to the 1.8 V cameras; all Mira220 modules answer at 0x54",TSSOP-24_4.4x7.8mm_P0.65mm
U6,1,STM32G0B1CBT6,STM32G0B1CBT6,STMicroelectronics,"Sync MCU, runs at 1.8 V; one timer drives all four camera triggers",LQFP-48_7x7mm_P0.5mm
U7,1,TXS0102,TXS0102DCUR,Texas Instruments,2-bit level translator 1.8 V <-> 3.3 V for the MAVLink UART,VSSOP-8_2.3x2mm_P0.5mm
U8,1,74LVC2G17,SN74LVC2G17DCKR,Texas Instruments,"Dual Schmitt buffer at 1.8 V, 5 V-tolerant inputs",SOT-363_SC-70-6
U9,1,MAX-M10S,MAX-M10S-00B,u-blox,GNSS receiver with time pulse (PPS); VIO_SEL to GND for 1.8 V I/O,ublox_MAX
U10,1,ICM-42688-P,ICM-42688-P,TDK InvenSense,"6-axis IMU, SPI, time-stamped by the sync MCU",LGA-14_3x2.5mm_P0.5mm_LayoutBorder3x4y
U11,1,USBLC6-2SC6,USBLC6-2SC6,STMicroelectronics,USB ESD protection,SOT-23-6
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
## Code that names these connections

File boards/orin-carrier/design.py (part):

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for k, v in CSI.items():
    jet(k, v)
jet("CAM_I2C_SCL", "I2C_CAM_SCL"); jet("CAM_I2C_SDA", "I2C_CAM_SDA")
jet("CAM0_PWDN", "CAM0_EN"); jet("CAM1_PWDN", "CAM1_EN"); jet("GPIO02", "CAM2_EN"); jet("GPIO03", "CAM3_EN")
jet("UART0_TXD", "MCU_UART_RX"); jet("UART0_RXD", "MCU_UART_TX")
jet("UART1_TXD", "TELEM_TX_1V8"); jet("UART1_RXD", "TELEM_RX_1V8")
jet("UART2_TXD", "DBG_TX"); jet("UART2_RXD", "DBG_RX")
jet("USB0_D_N", "USB_D_N"); jet("USB0_D_P", "USB_D_P")
jet("GPIO01/CLK", "USB_VBUS_DET")
jet("PCIE0_RX0_N", "PCIE_RX_N"); jet("PCIE0_RX0_P", "PCIE_RX_P")
jet("PCIE0_TX0_N", "PCIE_TX_C_N"); jet("PCIE0_TX0_P", "PCIE_TX_C_P")
jet("PCIE0_CLK_N", "PCIE_CLK_N"); jet("PCIE0_CLK_P", "PCIE_CLK_P")
jet("PCIE0_RST*", "PCIE_RST_N"); jet("PCIE0_CLKREQ*", "PCIE_CLKREQ_N"); jet("PCIE_WAKE*", "PCIE_WAKE_N")
jet("FORCE_RECOVERY*", "FORCE_RECOVERY_N")
jet("POWER_EN", "POWER_EN"); jet("SYS_RESET*", "SYS_RESET_N"); jet("SHUTDOWN_REQ*", "SHUTDOWN_REQ_N")
jet("GPIO09/AUD_MCLK", "PPS_1V8"); jet("GPIO11/CLK", "FRAME_SYNC")
jet("GPIO12/PWM", "MCU_NRST_REQ"); jet("GPIO13/PWM", "MCU_BOOT_REQ")
jet("I2C2_SCL", "I2C_ID_SCL"); jet("I2C2_SDA", "I2C_ID_SDA")

D.add("J2", None, "Jetson Orin Nano 8GB", "aviac:TE_2309413", J, B,
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M = {n: "NC" for n in range(1, 49)}
M.update({4: "+1V8", 5: "+1V8", 6: "+1V8", 7: GND,
          8: "MCU_OSC_IN", 9: "MCU_OSC_OUT", 10: "MCU_NRST",
          11: "VBAT_SENSE",          # PA0  ADC
          12: "FC_TRIG_1V8",         # PA1  TIM2_CH2 capture: autopilot camera trigger
          13: "MCU_UART_TX",         # PA2  USART2_TX -> Jetson UART0_RXD
          14: "MCU_UART_RX",         # PA3  USART2_RX <- Jetson UART0_TXD
          15: "IMU_CS_N", 16: "IMU_SCK", 17: "IMU_MISO", 18: "IMU_MOSI",   # PA4..PA7 SPI1
          19: "IMU_INT1",            # PB0
          20: "FC_FB_GATE",          # PB1  exposure feedback to autopilot
          21: "DLS_INT",             # PB2
          22: "GNSS_RXD",            # PB10 USART3_TX
          23: "GNSS_TXD",            # PB11 USART3_RX
          24: "LED_STAT_K",          # PB12 open-drain
          25: "POWER_EN",            # PB13 open-drain: pull low to switch the module off
          26: "SHUTDOWN_REQ_N",      # PB14
          27: "SYS_RESET_SENSE",     # PB15
          28: "TRIG0", 29: "TRIG1", 32: "TRIG2", 33: "TRIG3",   # PA8, PA9, PA10, PA11 = TIM1_CH1..4
          35: "SWDIO", 36: "SWCLK_BOOT0",
          37: "PPS_1V8",             # PA15 TIM2_CH1 capture: GNSS time pulse
          44: "FRAME_SYNC",          # PB5 -> Jetson GPIO11
          47: "DLS_SCL", 48: "DLS_SDA"})   # PB8/PB9 I2C1
D.add("U6", "MCU_ST_STM32G0:STM32G0B1CBTx", "STM32G0B1CBT6", "Package_QFP:LQFP-48_7x7mm_P0.5mm", M, B,
      mpn="STM32G0B1CBT6", mfr="STMicroelectronics", desc="Sync MCU, runs at 1.8 V; one timer drives all four camera triggers", mass=0.18)
for _ in range(3):
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      mpn="USBLC6-2SC6", mfr="STMicroelectronics", desc="USB ESD protection", mass=0.015)
D.C("USB_VBUS", GND, "100n", B, "0603", "50V")
D.R("USB_VBUS", "USB_VBUS_DET", "100k", B)
D.R("USB_VBUS_DET", GND, "56k", B)      # 5 V -> 1.8 V for the Jetson GPIO

# ===================================================================== MISC
B = "MISC"
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

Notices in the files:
parts and their libraries:
License: Apache-2.0
